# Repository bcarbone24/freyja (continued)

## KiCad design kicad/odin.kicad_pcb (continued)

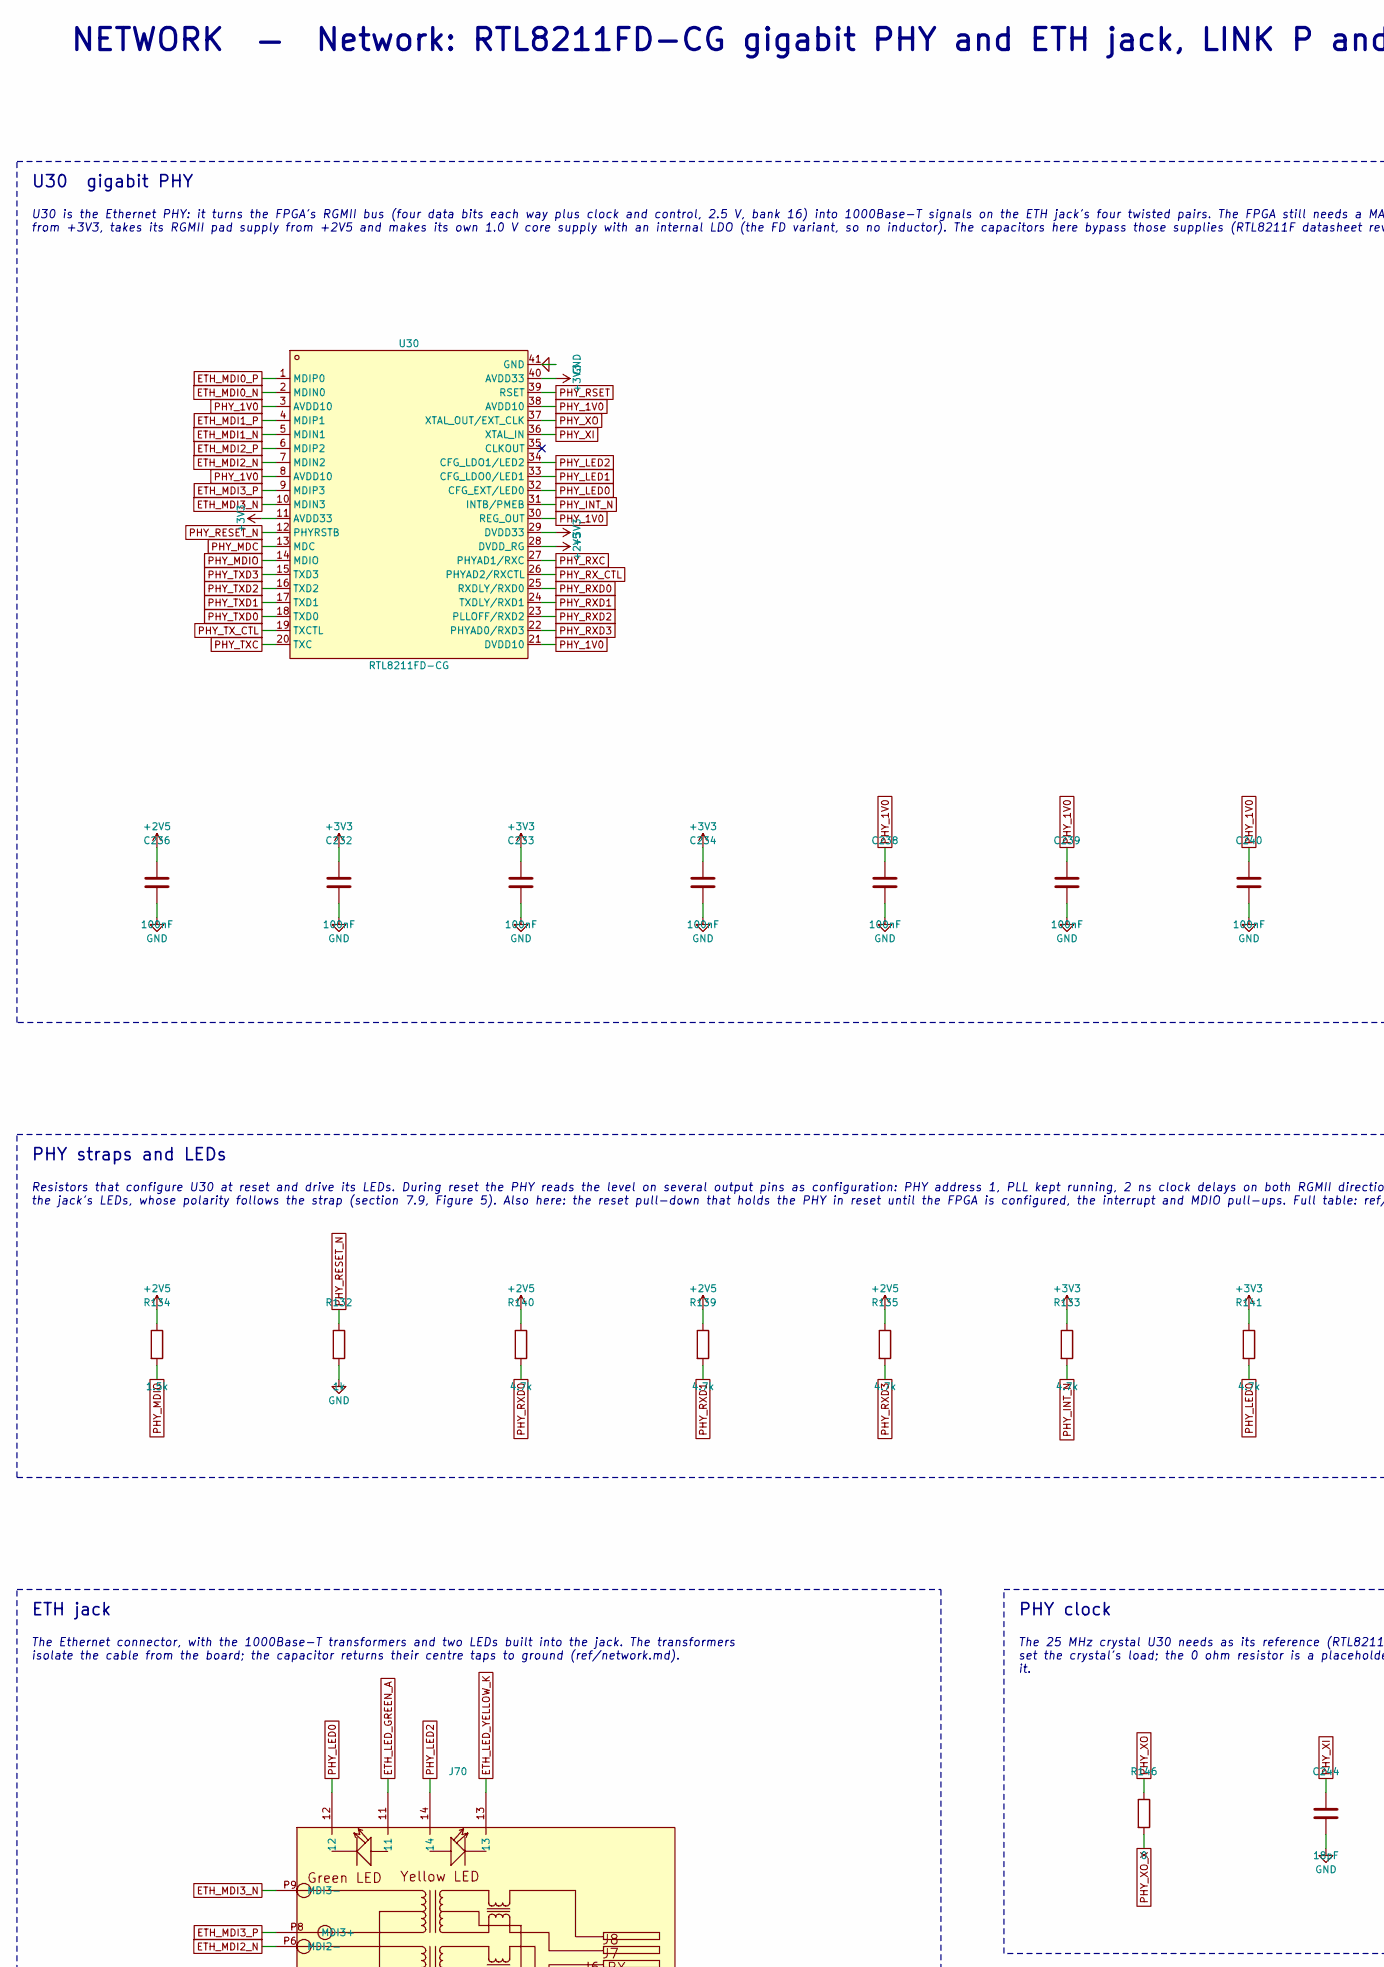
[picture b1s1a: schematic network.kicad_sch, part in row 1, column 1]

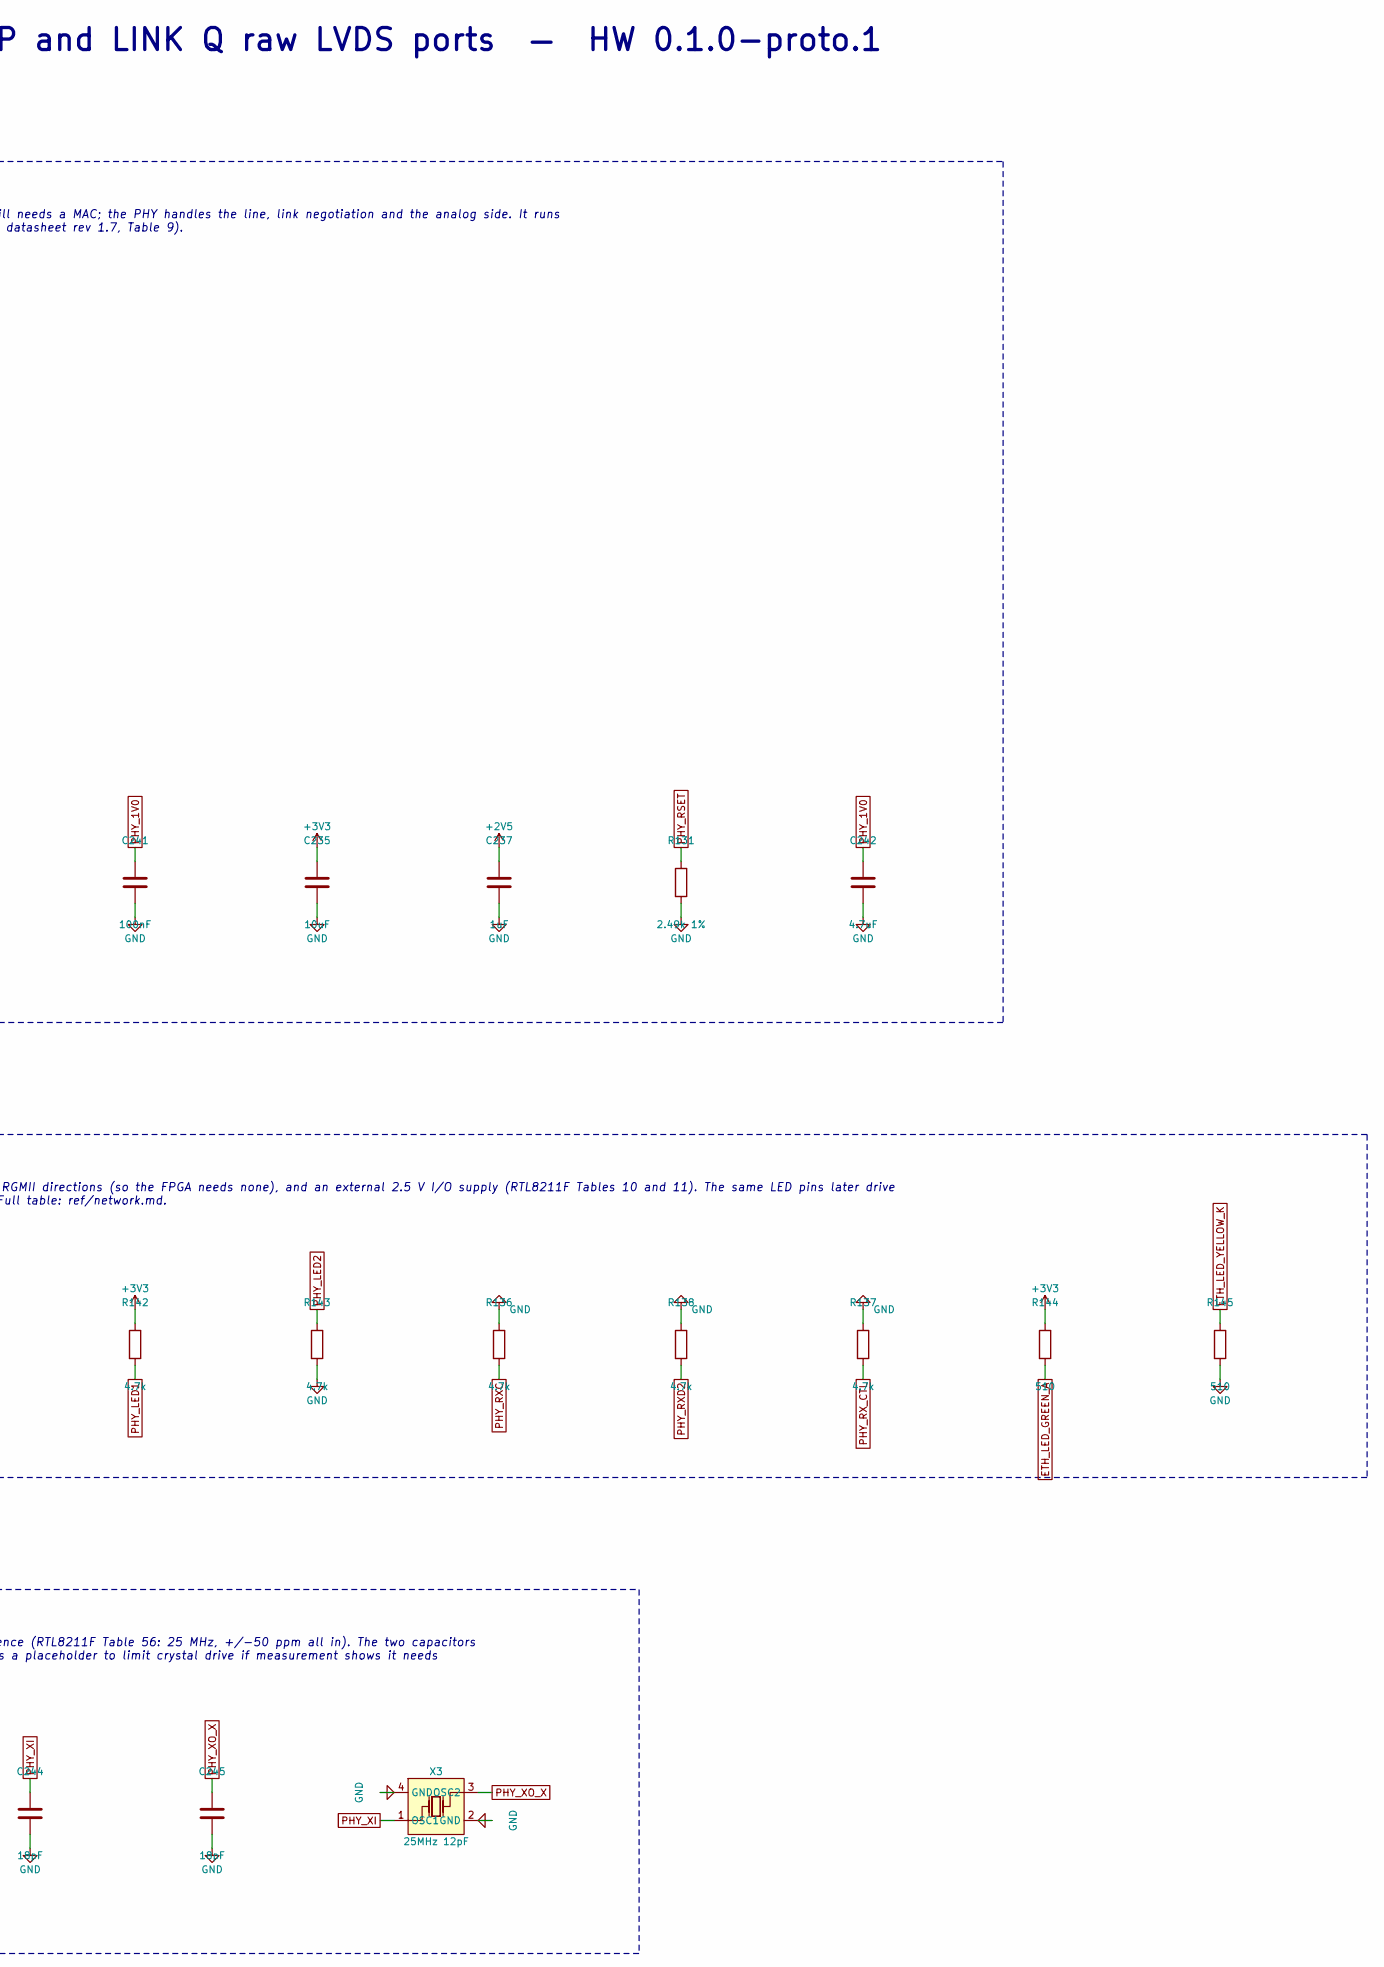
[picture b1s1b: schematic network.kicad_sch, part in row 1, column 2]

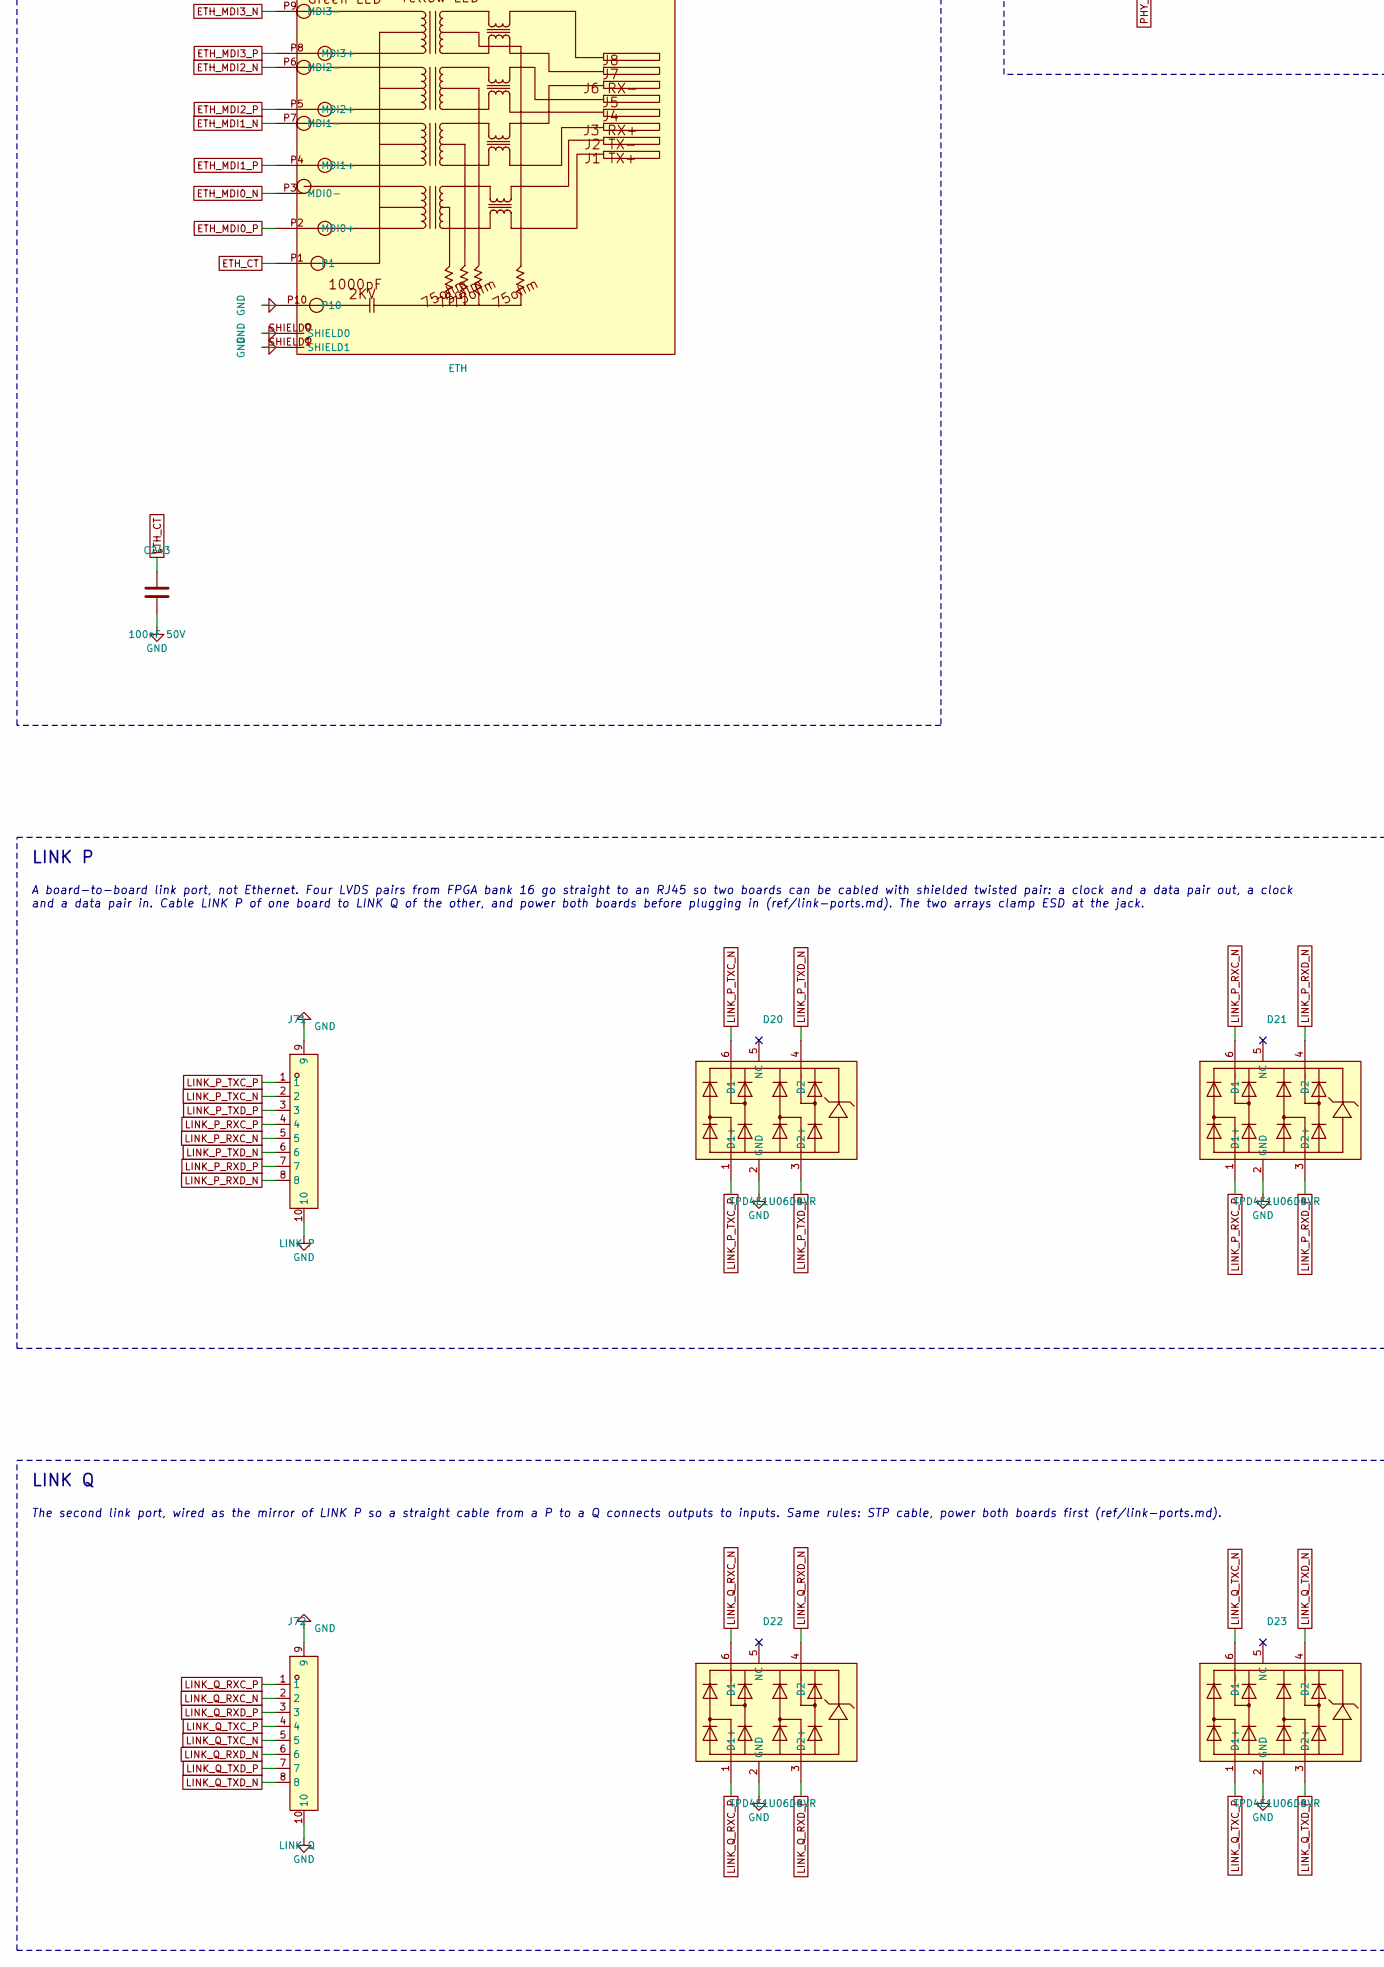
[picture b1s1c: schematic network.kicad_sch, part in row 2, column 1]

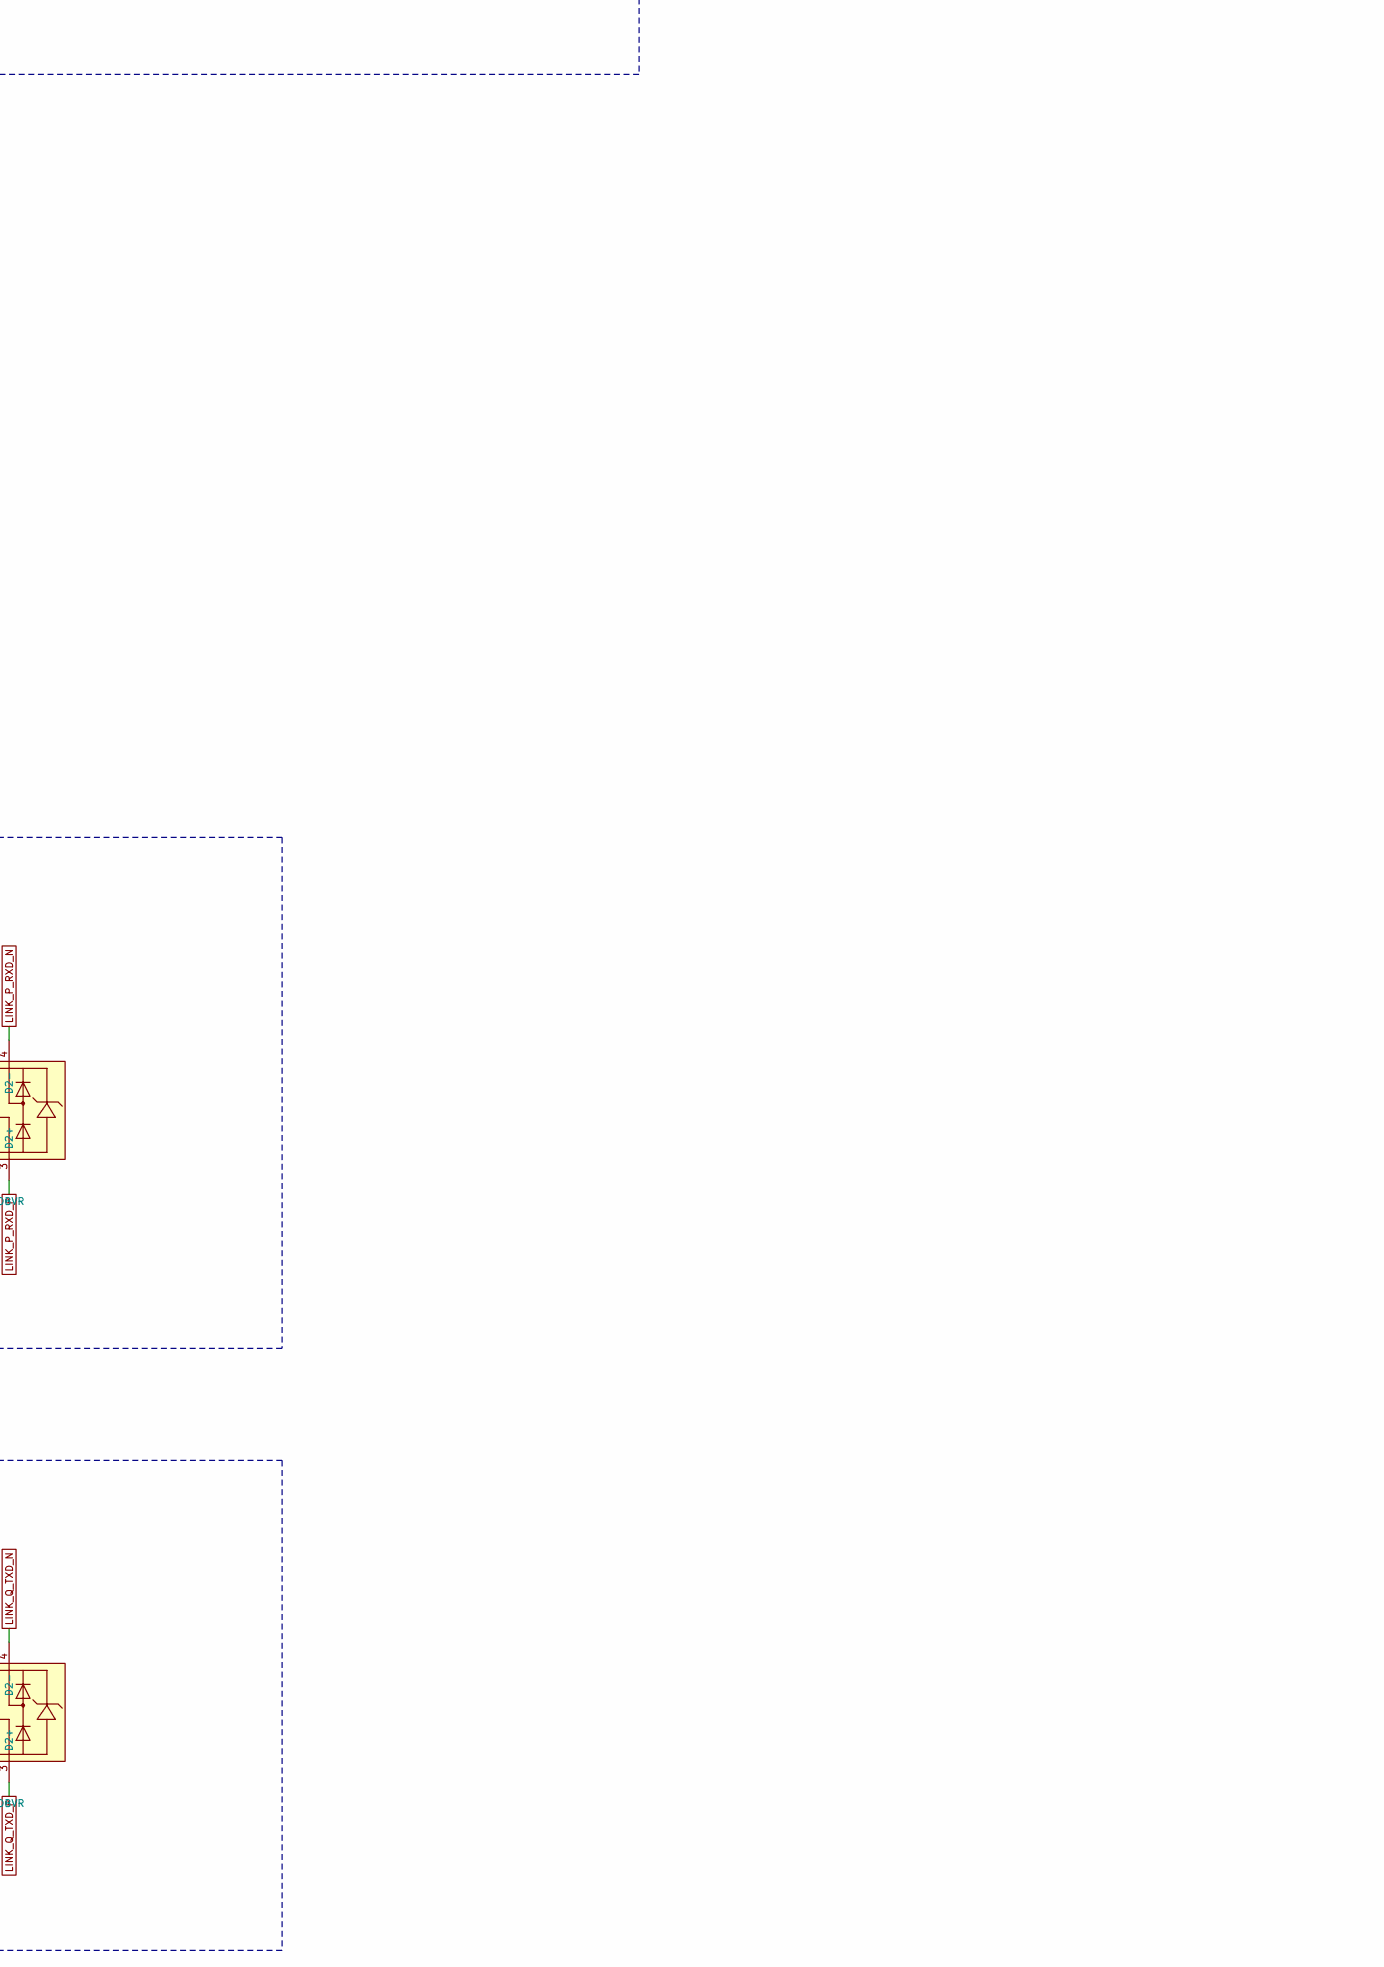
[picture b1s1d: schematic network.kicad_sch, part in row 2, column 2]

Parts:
C232, C233, C234, C236, C238, C239, C240, C241: 100nF; C_0402_1005Metric; LCSC C1525
C235: 10uF; C_0805_2012Metric; LCSC C15850
C237: 1uF; C_0603_1608Metric; LCSC C29936
C242: 4.7uF; C_0603_1608Metric; LCSC C277476
C243: 100nF 50V; C_0603_1608Metric
C244, C245: 18pF; C_0402_1005Metric
D20, D21, D22, D23: TPD4E1U06DBVR; SOT-23-6_L2.9-W1.6-P0.95-LS2.8-BR_TPD4E1U06; LCSC C124691
J70: ETH; RJ45-TH_HR911130A; LCSC C54408
J71: LINK P; RJ45-TH_KH-RJ45-58-8P8C; LCSC C2683360
J72: LINK Q; RJ45-TH_KH-RJ45-58-8P8C; LCSC C2683360
R131: 2.49k 1%; R_0402_1005Metric
R132: 1k; R_0402_1005Metric; LCSC C11702
R133, R135, R136, R137, R138, R139, R140, R141, R142, R143: 4.7k; R_0402_1005Metric; LCSC C25900
R134: 1.5k; R_0402_1005Metric
R144, R145: 510; R_0402_1005Metric
R146: 0; R_0402_1005Metric
U30: RTL8211FD-CG; QFN-40_L5.0-W5.0-P0.40-BL-EP3.7; LCSC C2687133
X3: 25MHz 12pF; CRYSTAL-SMD_4P-L3.2-W2.5-BL_X3225; LCSC C9006

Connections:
+2V5: C236.1, C237.1, R134.1, R135.1, R139.1, R140.1, U30.28 (DVDD_RG); also elsewhere on the board
+3V3: C232.1, C233.1, C234.1, C235.1, R133.1, R141.1, R142.1, R144.1, U30.11 (AVDD33), U30.29 (DVDD33), U30.40 (AVDD33); also elsewhere on the board
ETH_CT: C243.1, J70.P1
ETH_LED_GREEN_A: J70.11, R144.2
ETH_LED_YELLOW_K: J70.13, R145.1
ETH_MDI0_N: J70.P3 (MDI0-), U30.2 (MDIN0)
ETH_MDI0_P: J70.P2 (MDI0+), U30.1 (MDIP0)
ETH_MDI1_N: J70.P7 (MDI1-), U30.5 (MDIN1)
ETH_MDI1_P: J70.P4 (MDI1+), U30.4 (MDIP1)
ETH_MDI2_N: J70.P6 (MDI2-), U30.7 (MDIN2)
ETH_MDI2_P: J70.P5 (MDI2+), U30.6 (MDIP2)
ETH_MDI3_N: J70.P9 (MDI3-), U30.10 (MDIN3)
ETH_MDI3_P: J70.P8 (MDI3+), U30.9 (MDIP3)
GND: C232.2, C233.2, C234.2, C235.2, C236.2, C237.2, C238.2, C239.2, C240.2, C241.2, C242.2, C243.2, C244.2, C245.2, D20.2 (GND), D21.2 (GND), D22.2 (GND), D23.2 (GND), J70.P10, J70.SHIELD0, J70.SHIELD1, J71.9, J71.10, J72.9, J72.10, R131.2, R132.2, R136.1, R137.1, R138.1, R143.2, R145.2, U30.41 (GND), X3.2 (GND), X3.4 (GND); also elsewhere on the board
LINK_P_RXC_N: D21.6 (D1-), J71.5; also elsewhere on the board
LINK_P_RXC_P: D21.1 (D1+), J71.4; also elsewhere on the board
LINK_P_RXD_N: D21.4 (D2-), J71.8; also elsewhere on the board
LINK_P_RXD_P: D21.3 (D2+), J71.7; also elsewhere on the board
LINK_P_TXC_N: D20.6 (D1-), J71.2; also elsewhere on the board
LINK_P_TXC_P: D20.1 (D1+), J71.1; also elsewhere on the board
LINK_P_TXD_N: D20.4 (D2-), J71.6; also elsewhere on the board
LINK_P_TXD_P: D20.3 (D2+), J71.3; also elsewhere on the board
LINK_Q_RXC_N: D22.6 (D1-), J72.2; also elsewhere on the board
LINK_Q_RXC_P: D22.1 (D1+), J72.1; also elsewhere on the board
LINK_Q_RXD_N: D22.4 (D2-), J72.6; also elsewhere on the board
LINK_Q_RXD_P: D22.3 (D2+), J72.3; also elsewhere on the board
LINK_Q_TXC_N: D23.6 (D1-), J72.5; also elsewhere on the board
LINK_Q_TXC_P: D23.1 (D1+), J72.4; also elsewhere on the board
LINK_Q_TXD_N: D23.4 (D2-), J72.8; also elsewhere on the board
LINK_Q_TXD_P: D23.3 (D2+), J72.7; also elsewhere on the board
PHY_1V0: C238.1, C239.1, C240.1, C241.1, C242.1, U30.3 (AVDD10), U30.8 (AVDD10), U30.21 (DVDD10), U30.30 (REG_OUT), U30.38 (AVDD10)
PHY_INT_N: R133.2, U30.31 (INTB/PMEB); also elsewhere on the board
PHY_LED0: J70.12, R141.2, U30.32 (CFG_EXT/LED0)
PHY_LED1: R142.2, U30.33 (CFG_LDO0/LED1)
PHY_LED2: J70.14, R143.1, U30.34 (CFG_LDO1/LED2)
PHY_MDC: U30.13 (MDC); also elsewhere on the board
PHY_MDIO: R134.2, U30.14 (MDIO); also elsewhere on the board
PHY_RESET_N: R132.1, U30.12 (PHYRSTB); also elsewhere on the board
PHY_RSET: R131.1, U30.39 (RSET)
PHY_RXC: R136.2, U30.27 (PHYAD1/RXC); also elsewhere on the board
PHY_RXD0: R140.2, U30.25 (RXDLY/RXD0); also elsewhere on the board
PHY_RXD1: R139.2, U30.24 (TXDLY/RXD1); also elsewhere on the board
PHY_RXD2: R138.2, U30.23 (PLLOFF/RXD2); also elsewhere on the board
PHY_RXD3: R135.2, U30.22 (PHYAD0/RXD3); also elsewhere on the board
PHY_RX_CTL: R137.2, U30.26 (PHYAD2/RXCTL); also elsewhere on the board
PHY_TXC: U30.20 (TXC); also elsewhere on the board
PHY_TXD0: U30.18 (TXD0); also elsewhere on the board
PHY_TXD1: U30.17 (TXD1); also elsewhere on the board
PHY_TXD2: U30.16 (TXD2); also elsewhere on the board
PHY_TXD3: U30.15 (TXD3); also elsewhere on the board
PHY_TX_CTL: U30.19 (TXCTL); also elsewhere on the board
PHY_XI: C244.1, U30.36 (XTAL_IN), X3.1 (OSC1)
PHY_XO: R146.1, U30.37 (XTAL_OUT/EXT_CLK)
PHY_XO_X: C245.1, R146.2, X3.3 (OSC2)

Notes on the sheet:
NETWORK — Network: RTL8211FD-CG gigabit PHY and ETH jack, LINK P and LINK Q raw LVDS ports — HW 0.1.0-proto.1
U30 gigabit PHY
U30 is the Ethernet PHY: it turns the FPGA's RGMII bus (four data bits each way plus clock and control, 2.5 V, bank 16) into 1000Base-T signals on the ETH jack's four twisted pairs. The FPGA still needs a MAC; the PHY handles the line, link negotiation and the analog side. It runs from +3V3, takes 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
PHY straps and LEDs
Resistors that configure U30 at reset and drive its LEDs. During reset the PHY reads the level on several output pins as configuration: PHY address 1, PLL kept running, 2 ns clock delays on both RGMII directions (so the FPGA needs none), and an external 2.5 V I/O supply (RTL8211F Tables 10 and 11).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
ETH jack
The Ethernet connector, with the 1000Base-T transformers and two LEDs built into the jack. The transformers isolate the cable from the board; the capacitor returns their centre taps to ground (ref/network.md).
PHY clock
The 25 MHz crystal U30 needs as its reference (RTL8211F Table 56: 25 MHz, +/-50 ppm all in). The two capacitors set the crystal's load; the 0 ohm resistor is a placeholder to limit crystal drive if measurement shows it needs it.
LINK P
A board-to-board link port, not Ethernet. Four LVDS pairs from FPGA bank 16 go straight to an RJ45 so two boards can be cabled with shielded twisted pair: a clock and a data pair out, a clock and a data pair in. Cable LINK P of one board to LINK Q of the other, and power both boards before plugging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
LINK Q
The second link port, wired as the mirror of LINK P so a straight cable from a P to a Q connects outputs to inputs. Same rules: STP cable, power both boards first (ref/link-ports.md).

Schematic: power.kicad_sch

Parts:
C184: 2.2nF 25V; C_0402_1005Metric
C185, C186, C192, C267: 10uF 50V; C_1210_3225Metric; LCSC C77102
C187: 10uF 25V; C_0805_2012Metric; LCSC C15850
C188, C193, C200, C203, C206, C225, C226, C227, C228, C229, C230, C262, C263, C271, C274, C277, C278: 100nF; C_0402_1005Metric; LCSC C1525
C189, C190, C191, C195, C196, C197, C198, C199, C201, C202, C204, C205, C207, C211, C212, C265, C266: 22uF; C_0805_2012Metric; LCSC C86816
C194: 56pF; C_0402_1005Metric
C208, C218, C219, C220, C221, C273, C276, C280: 1uF; C_0603_1608Metric; LCSC C29936
C209: 1nF; C_0402_1005Metric
C210: 22pF; C_0402_1005Metric
C224, C268, C269, C270: 4.7uF; C_0603_1608Metric; LCSC C277476
C261, C279: 10uF; C_0805_2012Metric; LCSC C15850
C264: 100nF 25V; C_0402_1005Metric; LCSC C1525
C272, C275: 1nF 50V; C_0402_1005Metric
D3, D4: SS34; SMA_L4.3-W2.6-LS5.2-RD; LCSC C8678
D8: SMBJ22A; D_SMB; LCSC C151920
D24: 1N4148W; D_SOD-123; LCSC C81598
FB1: 120R 2A BLM18PG121SN1D; L_0603_1608Metric; LCSC C14709
J50: 9-21V POWER IN; CONN-TH_P5.00_KF301-5.0-2P; LCSC C474881
J68: AUX IN 9-28V UNREGULATED; CONN-TH_P5.00_KF301-5.0-2P; LCSC C474881
L2, L3: 4.7uH SRN6045TA-4R7M; IND-SMD_L6.0-W6.0; LCSC C2044594
L4, L5, L6: 2.2uH SRN4018-2R2M; IND-SMD_L4.0-W4.0_SNR4018; LCSC C913207
L7: 1uH_core FTC201610S1R0MBCA; IND-SMD_L2.0-W1.6-B; LCSC C5832342
L9: 1uH VLS252010HBX-1R0M-1; IND-SMD_L2.5-W2.0-1; LCSC C88211
Q6, Q7: BSS138LT1G; SOT-23-3_L2.9-W1.6-P1.90-LS2.8-BR; LCSC C82045
R50, R55, R59, R61, R63, R64, R67, R72, R81, R83, R91, R93, R94, R162, R164, R166, R201: 100k; R_0603_1608Metric
R51, R84: 47k; R_0603_1608Metric
R52: 73.2k; R_0603_1608Metric
R53, R73, R169: 10k; R_0603_1608Metric
R54: 1.65k; R_0603_1608Metric
R56: 19.1k; R_0603_1608Metric
R57: 93.1k; R_0603_1608Metric
R58: 30.1k; R_0603_1608Metric
R60: 31.6k; R_0603_1608Metric
R62: 49.9k; R_0603_1608Metric
R65: 10; R_0603_1608Metric
R66: 100k; R_0402_1005Metric; LCSC C25741
R68: 150k; R_0603_1608Metric
R74: 1.15k; R_0603_1608Metric
R75: 2.21k; R_0603_1608Metric
R82: 16k; R_0603_1608Metric
R85, R86, R87, R88, R198, R199: 1k; R_0603_1608Metric
R163: 36.5k; R_0603_1608Metric
R165: 23.2k; R_0603_1608Metric
R167: 56.2k; R_0603_1608Metric
R168: 44.2k; R_0603_1608Metric
R200: 470k; R_0603_1608Metric
R202: 33k; R_0603_1608Metric
U11, U12: AP63300WU-7; TSOT-23-6_L2.9-W1.6-P0.95-LS2.8-BR; LCSC C2158012
U13, U14, U16: TLV62569DRLR; SOT-563_L1.6-W1.2-P0.50-LS1.6-BL; LCSC C163217
U15: SY8047QDC; TQFN-16_L3.0-W3.0-P0.50-TL-EP1.6; LCSC C3018651
U21, U22: TPS22950CDDCR; SOT-23-6_L2.9-W1.6-P0.95-LS2.8-BL_3; LCSC C7587833
U23, U24: TPS22953DSQR; Texas_DSQ0010A_WSON-10-1EP_2x2mm_P0.4mm_EP0.9x1.5mm; LCSC C2680343
U26: TPS259470ARPWR; Texas_RPU0010A_VQFN-HR-10_2x2mm_P0.5mm; LCSC C3662799
U34: TPS2121RUXR; Texas_VQFN-HR-12_2x2.5mm_P0.5mm; LCSC C485916

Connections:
+1V0: C210.1, C211.1, C212.1, L7.1, L9.2, R67.1, R88.1; also elsewhere on the board
+1V0_MGT: C224.1, L9.1; also elsewhere on the board
+1V2_MGT: C204.1, C205.1, L6.1, R63.1; also elsewhere on the board
+1V8: FB1.2, R87.1; also elsewhere on the board
+1V8_IO: C201.1, C202.1, C261.1, C262.1, FB1.1, L5.1, R61.1; also elsewhere on the board
+2V5: C198.1, C199.1, L4.1, R59.1, R86.1; also elsewhere on the board
+3V3: C194.1, C195.1, C196.1, C197.1, C219.1, C271.1, C274.1, L3.1, R57.1, R66.1, R73.1, R85.1, R166.1, R169.1, U22.2 (VIN), U23.3 (BIAS), U24.3 (BIAS); also elsewhere on the board
+3V3_EXT: U22.5 (VOUT); also elsewhere on the board
+5V: C200.1, C203.1, C206.1, C207.1, C218.1, C265.1, C266.1, C268.1, C269.1, C270.1, R65.1, R83.1, U13.3 (VIN), U14.3 (VIN), U14.5 (EN), U15.11 (PVIN), U15.12 (PVIN), U16.3 (VIN), U21.2 (VIN), U34.1 (OUT), U34.8 (OUT); also elsewhere on the board
+5V_BUCK: C189.1, C190.1, C191.1, C280.1, L2.1, R55.1, U34.2 (IN2)
+5V_EXT: U21.5 (VOUT); also elsewhere on the board
AUX_RAIL: J68.1; also elsewhere on the board
BOOT_3V3: C193.1, U12.6 (BST)
BOOT_5V: C188.1, U11.6 (BST)
CORE_1V0_GOOD: R66.2, U15.4 (PG); also elsewhere on the board
CORE_1V0_SS: C209.1, U15.9 (SS)
CORE_1V0_SVIN: C208.1, R65.2, U15.10 (SVIN)
EN_1V0: R94.1, U15.13 (EN); also elsewhere on the board
EN_1V2: R93.1, U16.5 (EN); also elsewhere on the board
EN_2V5: R91.1, U13.5 (EN); also elsewhere on the board
EXT_EN: R72.1, U21.1 (ON), U22.1 (ON), U23.4 (EN), U24.4 (EN); also elsewhere on the board
EXT_FAULT: R73.2, U21.6 (FLT), U22.6 (FLT), U26.4 (FLT); also elsewhere on the board
EXT_PRESENT: Q7.1 (G), R201.2, R202.1
FB+1V0: C210.2, R67.2, R68.1, U15.5 (FB)
FB+1V2_MGT: R63.2, R64.1, U16.1 (FB)
FB+1V8_IO: R61.2, R62.1, U14.1 (FB)
FB+2V5: R59.2, R60.1, U13.1 (FB)
FB_3V3: C194.2, R57.2, R58.1, U12.1 (FB)
FB_5V: R55.2, R56.1, U11.1 (FB)
GND: C184.2, C185.2, C186.2, C187.2, C189.2, C190.2, C191.2, C192.2, C195.2, C196.2, C197.2, C198.2, C199.2, C200.2, C201.2, C202.2, C203.2, C204.2, C205.2, C206.2, C207.2, C208.2, C209.2, C211.2, C212.2, C218.2, C219.2, C220.2, C221.2, C224.2, C225.2, C226.2, C227.2, C228.2, C229.2, C230.2, C261.2, C262.2, C263.2, C264.2, C265.2, C266.2, C267.2, C268.2, C269.2, C270.2, C271.2, C272.2, C273.2, C274.2, C275.2, C276.2, C277.2, C278.2, C279.2, C280.2, D8.2 (A), J50.2, J68.2, Q6.2 (S), Q7.2 (S), R51.2, R53.2, R54.2, R56.2, R58.2, R60.2, R62.2, R64.2, R68.2, R72.2, R74.2, R75.2, R82.2, R84.2, R91.2, R93.2, R94.2, R163.2, R165.2, R167.2, R168.2, R200.2, R202.2, U11.4 (GND), U12.4 (GND), U13.2 (GND), U14.2 (GND), U15.6 (AGND), U15.14 (PGND), U15.15 (PGND), U15.17 (EP), U16.2 (GND), U21.3 (GND), U22.3 (GND), U23.5 (GND), U23.7 (PG), U23.11 (EP), U24.5 (GND), U24.7 (PG), U24.11 (EP), U26.8 (GND), U34.4 (OV2), U34.12 (GND); also elsewhere on the board
MON_1V0: C230.1, R88.2; also elsewhere on the board
MON_1V8: C229.1, R87.2; also elsewhere on the board
MON_2V5: C228.1, R86.2; also elsewhere on the board
MON_3V3: C227.1, R85.2; also elsewhere on the board
MON_5V: C226.1, R83.2, R84.1; also elsewhere on the board
MON_VCCIO_1: C277.1, R198.2; also elsewhere on the board
MON_VCCIO_2: C278.1, R199.2; also elsewhere on the board
MON_VSYS: C225.1, R81.2, R82.1; also elsewhere on the board
PD_REQ_9V: D24.2 (A); also elsewhere on the board
SEL_IN2: C279.1, D24.1 (K), Q6.1 (G), R200.1
SW+1V0: L7.2, U15.1 (LX), U15.2 (LX)
SW+1V2_MGT: L6.2, U16.4 (SW)
SW+1V8_IO: L5.2, U14.4 (SW)
SW+2V5: L4.2, U13.4 (SW)
SW_3V3: C193.2, L3.2, U12.5 (SW)
SW_5V: C188.2, L2.2, U11.5 (SW)
U21_ILIM: R74.1, U21.4 (ILIM)
U22_ILIM: R75.1, U22.4 (ILIM)
U23_CT: C272.1, U23.6 (CT)
U24_CT: C275.1, U24.6 (CT)
VBUS: C187.1, C264.1, R50.1, R52.1, R162.1, R164.1, U26.5 (IN), U34.7 (IN1); also elsewhere on the board
VBUS5_CP2: R166.2, R167.1, U34.3 (CP2)
VBUS5_ILIM: R168.1, U34.10 (ILIM)
VBUS5_OV1: R164.2, R165.1, U34.5 (OV1)
VBUS5_PR1: Q6.3 (D), Q7.3 (D), R162.2, R163.1, U34.6 (PR1)
VBUS5_SS: C263.1, U34.11 (SS)
VBUS5_ST: R169.2, U34.9 (ST); also elsewhere on the board
VBUS_DVDT: C184.1, U26.7 (dVdt)
VBUS_ILM: R54.1, U26.9 (ILM)
VBUS_OVLO: R52.2, R53.1, U26.2 (OVLO)
VBUS_SS: D3.2 (A), U26.6 (OUT)
VBUS_UVLO: R50.2, R51.1, U26.1 (EN/UVLO)
VCCIO_1: C220.1, R198.1, U23.1 (IN), U23.2 (IN); also elsewhere on the board
VCCIO_1_EXT: C273.1, U23.8 (SNS), U23.9 (OUT), U23.10 (OUT); also elsewhere on the board
VCCIO_2: C221.1, R199.1, U24.1 (IN), U24.2 (IN); also elsewhere on the board
VCCIO_2_EXT: C276.1, U24.8 (SNS), U24.9 (OUT), U24.10 (OUT); also elsewhere on the board
VIN_EXT: D4.2 (A), D8.1 (K), J50.1, R201.1
VSYS: C185.1, C186.1, C192.1, C267.1, D3.1 (K), D4.1 (K), R81.1, U11.3 (VIN), U12.3 (VIN)

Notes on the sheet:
POWER — Power tree: VSYS input, regulators, AUX IN pass-through and monitoring — HW 0.1.0-proto.1
input OR-ing
Where power enters. Two inputs feed one internal supply, VSYS: USB-C (5 V, or 9 V when a USB-PD charger agrees) and the J50 screw terminal (9-21 V). A diode on each (D3, D4) lets whichever is higher supply the board and stops one input from back-feeding the other. On the USB side, U26 is an electro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
U11 VSYS to +5V
Switching regulator (buck converter) that makes +5V from VSYS. It runs whenever power is present (no enable), like U12, so the FPGA's 1.8 V auxiliary supply is never missing while its 3.3 V banks are powered. Its output goes to the +5V rail through U34. +5V feeds the 5 V buses, the extension 5 V pi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
U12 VSYS to +3V3 (always-on AP63300 reference circuit)
Switching regulator that makes +3V3 from VSYS. It has no enable: it starts as soon as any power is present, because +3V3 runs the board controller, which then switches everything else on. Also powers the PSRAM, the flashes, the PHY and most logic. The two feedback resistors set 3.3 V; the inductor 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
U13 5V to +2V5
Small switching regulator that makes +2V5 from +5V for FPGA bank 16 (network) and the PHY's RGMII pins. Enabled by the board controller (EN_2V5); the feedback resistors set 2.5 V.
U14 5V to +1V8_IO
Small switching regulator that makes 1.8 V from +5V. Its output node is +1V8_IO: FPGA bank 13 and the 1.8 V memory on it, the 1.8 V position of the J19/J20 jumpers, and, through the bead below, the FPGA's auxiliary supply (VCCAUX) and its ADC as +1V8. Its enable is tied to +5V, so it runs whenever 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
U16 5V to +1V2_MGT
Small switching regulator that makes +1V2_MGT from +5V for the FPGA transceivers' MGTAVTT supply. The transceivers are unused in rev A but must stay powered. Enabled by the board controller (EN_1V2).
U15 5V to +1V0 (4A FPGA core supply)
The FPGA core supply: up to 4 A at 1.0 V from +5V, the heaviest rail on the board. Enabled by the board controller (EN_1V0); its power-good output (CORE_1V0_GOOD) goes to the board controller (GPIO38) so firmware knows the core is up. The soft-start capacitor makes it ramp slowly; the feedback resi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
extension power protection control
Shared control for the four protected extension supplies (U21-U24). EXT_EN, from the board controller, turns them all on; the pull-down keeps them off until firmware decides. EXT_FAULT is pulled up and goes low if any of them (or the USB eFuse) detects a fault, so one controller pin hears all of th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
U21 +5V to +5V_EXT
Protected switch between the board's +5V and the 5 V pins of every extension port. Limits current to about 1 A and blocks current flowing back from an extension. Without it, a shorted extension would pull the whole board's 5 V down.
U22 +3V3 to +3V3_EXT
Protected switch between +3V3 and the 3.3 V pins of every extension port, limited to about 0.5 A, with reverse blocking. Keeps a faulty extension from taking down the board controller's supply.
U23 VCCIO_1 to VCCIO_1_EXT
Switch for the PIN V supply of slots A-D (the voltage chosen on J19). It is biased from +3V3 so it works down to the 1.8 V setting, blocks current flowing back in while off, ramps its output in about 1.5 ms and shuts down when hot. Overload protection is each slot's 500 mA fuse; the switch itself h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
U24 VCCIO_2 to VCCIO_2_EXT
Switch for the PIN V supply of slots E-H (the voltage chosen on J20). It is biased from +3V3 so it works down to the 1.8 V setting, blocks current flowing back in while off, ramps its output in about 1.5 ms and shuts down when hot. Overload protection is each slot's 500 mA fuse; the switch itself h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
MGTAVCC filter
A small inductor and capacitor that make +1V0_MGT from +1V0: the same voltage, with the core's switching noise filtered out, for the transceivers' MGTAVCC supply.
rail monitors
Lets the board controller measure every supply. Each rail goes to one of its eight analog inputs (ADC), which read 0-3.3 V. Rails at or below 3.3 V go through a 1 k resistor that protects the pin; VSYS and +5V are higher, so two resistors divide them down first. A 100 nF capacitor on each input ste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
AUX IN
Optional extra power for extensions that need more than 5 V (motors, LED strips, displays). Whatever you connect here (9-28 V DC) goes, unregulated, to the AUX pin of every extension port through each port's own fuse. The board itself never uses it.
VCCAUX filter
The split between +1V8_IO and +1V8. VCCAUX and VCCADC are the FPGA's internal supplies (clocking, I/O pre- drivers, the XADC) and should not share copper with switching 1.8 V I/O loads, so they hang off U14's output through one ferrite bead (120 ohm at 100 MHz, 2 A, 50 mohm: 9 mV at the 0.18 A VCCA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
U34 +5V source select
Chooses what feeds the +5V rail: USB power straight from the connector, or U11. A regulator cannot make 5 V out of 5 V, so on a plain 5 V USB source the mux passes VBUS to the rail. It hands the rail to U11 while the board controller asks the charger for 9 V and for a few seconds after (Q6), while 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
Q6 mux hold: 9 V request
Keeps U34 on U11 around a 9 V negotiation. The controller's 9 V request charges a capacitor through D24 at once and the capacitor drains through its resistor in 2-7 s, so the rail leaves VBUS before the charger moves it and returns only when VBUS is back at 5 V. No voltage threshold can do that wit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
Q7 mux hold: screw input present
Keeps U34 on U11 whenever the screw input carries voltage, so a bench supply on J50 carries the whole board even with a 5 V USB cable plugged in; before, the USB port kept the 5 V load.
Power flags for the rails made on this page
